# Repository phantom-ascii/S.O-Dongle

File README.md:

# S.O Dongle 
## -by a 14 yr old kid

## Overview:
### A fully diy dongle that shows your pcs stats(such as ram and cpu usage) on a 0.91 oled display.

This project was made fully by me for the #dongle program on hackclub.com. Thx to the team for hosting this program
Ive always had a love for creating and tech so when you put the 2 together you  get hardware and hence i am here creating a dongle with softwares ive never touched before but its all part of the journey.
At the moment the software is only written for Ubuntu (my daily driver) but i may write some for other os'.

Anyway here is some eye candy:

Now we are done with that here is the bom:

**Bill of Materials (BOM) & Vendor Shipping**

| Item # | Part Name / Description | Qty Ordered | Item Cost ($) | Vendor Shipping Cost ($) | Source & Link |
| :---: | :--- | :---: | :---: | :---: | :--- |
| **1** | CH552G 8-bit USB Microcontroller (`U1`) | 1 pc | $0.75 | $8.25 *(LCSC S&H)* | [LCSC (C111292)](https://www.lcsc.com/search?q=C111292) |
| **2** | 100nF Decoupling Capacitors (`C1`, `C2`) | 50 pcs | $0.76 | $8.25 *(LCSC S&H)* | [LCSC (C14663)](https://www.lcsc.com/search?q=C14663) |
| **3** | 10kΩ Chip Resistor (`R1`) | 100 pcs | $0.48 | $8.25 *(LCSC S&H)* | [LCSC (C25804)](https://www.lcsc.com/search?q=C25804) |
| **4** | SMD Tactile Push Button (`SW1`) | 50 pcs | $0.95 | $8.25 *(LCSC S&H)* | [LCSC (C2837531)](https://www.lcsc.com/search?q=C2837531) |
| **5** | 0.91" I2C OLED Display Module (128x32, 4-pin) | 1 pc | $0.99 | $0.00 *(Free)* | [AliExpress](https://www.aliexpress.com/item/1005003727192340.html) |
| **6** | USB-A Edge Connector (`J1`) | 1 pc | $0.00 | $0.00 | Integrated on PCB |
| **7** | Custom 3D Printed Case & Lid (`Case.step` + `Lid.step`) | 1 set | $0.74 | $21.32 *(JLCPCB)* | [JLCPCB 3DP](https://jlcpcb.com/3d-printing) |
| **8** | Custom PCB Prototype (White, ENIG Finish, Qty 5) | 5 boards | $20.70 | $21.32 *(JLCPCB)* | [JLCPCB](https://jlcpcb.com) |

---

**Cart & Checkout Totals Breakdown**

* **LCSC Cart Total:** **$11.19** ($2.94 parts + $5.25 shipping + $3.00 handling fee)
* **AliExpress Cart Total:** **$0.99** ($0.99 parts + $0.00 shipping)
* **JLCPCB Cart Total:** **$22.76** ($21.44 parts + $21.32 shipping - $20.00 coupon discount)
* **Combined Grand Total:** **$34.94**
---

## Manufacturing & Assembly

1. **PCBs & 3D Prints:** Ordered via [JLCPCB](https://jlcpcb.com) (White solder mask, ENIG finish) and [JLCPCB 3DP](https://jlcpcb.com/3d-printing) (9600 Resin, White).
2. **Electronics & Switch:** Microcontroller, passives, and tactile switch ordered via [LCSC](https://www.lcsc.com).
3. **Display:** 0.91" 4-pin I2C OLED display ordered via [AliExpress](https://www.aliexpress.com).
4. **Hand Soldering EVERYTHING**

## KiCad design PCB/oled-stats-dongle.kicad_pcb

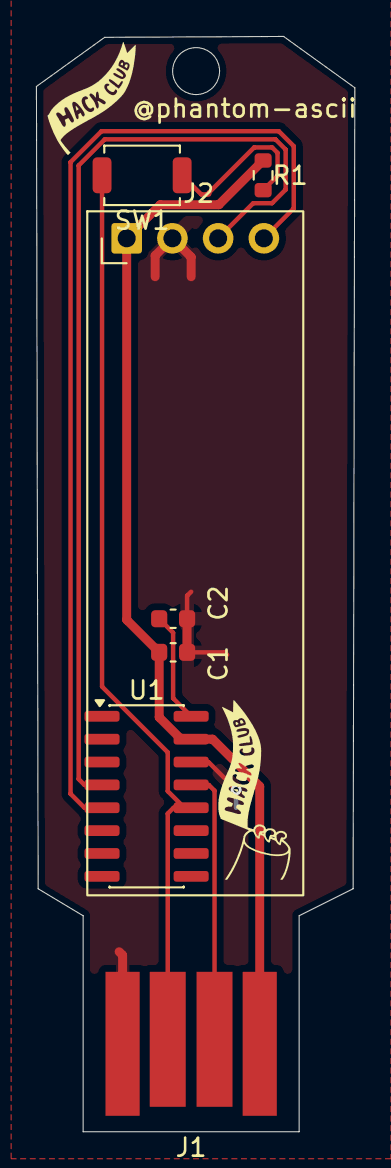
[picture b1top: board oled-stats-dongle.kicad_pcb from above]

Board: 2 copper layers, 17.7 x 60.8 mm, 7 parts (0 on the bottom side), 8 nets.

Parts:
C1, C2: 100nF; C_0603_1608Metric
J1: USB_A; USB-A
J2: Conn_01x04; ER_OLEDM0.91_1x-I2C
R1: 10k; R_0603_1608Metric
SW1: SW_Push; SW_SPST_TS-1088-xR020
U1: CH552G; SOIC-16_3.9x9.9mm_P1.27mm

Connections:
/D+: J1.3 (D+), SW1.1, U1.12 (P3.6)
/D-: J1.2 (D-), U1.13 (P3.7)
/SCL: J2.3, U1.4 (P1.6)
/SDA: J2.4, U1.5 (P1.7)
GND: C1.2, C2.1, J1.4 (GND), J2.2, U1.14 (GND)
unnamed: R1.2, SW1.2
unnamed: C2.2, U1.16 (3V3)
VBUS: C1.1, J1.1 (VBUS), J2.1, R1.1, U1.15 (VCC)
